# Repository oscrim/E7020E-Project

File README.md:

# E7020E-Project

# E-Toaster
Design and build a PCB to upgrade a toaster to an e-Toaster !

# Prerequisites 

* Archlinux
* Visual studio

# Implementation

For the software part we will use RUST to program the MCU.
Build with :
* Cargo
* OpenOCD

# Components

## General
* 1: Nucleo board to program our own board
* 1: USB Mini-B connector
* 1: bluetooth sensor RN 42 Series Class 2
* 1: STM32F411RET6 MCU
* 1: LM1117IMP-ADJ voltage converter
* 3: 6pins header
* 1: temp sensor LMT84
* 1: LCD screen EA DOGS102W-6
* 2: red LEDs
* 1: green LED
* 2: pushbuttons
* 2: transistors
* 1: relay 5V-230V

## Capacitors
* 2: 4.7u
* 12:  100n
* 5:   1u
* 2:   18p
* 1:   0.01u
* 2:   10u polarized

## Resistors
* 2:            4.7k
* 3:   10k
* 5:   100
* 1:   5k
* 2:   470
* 4:   3.3k
* 2:   1k
* 1:   820
* 1:   160

# Authors 

* **SCHRUB Valentin** - Hardware design and realization.

* **ROMARY Lucas** - Hardware design and realization.

* **FRISENSTAM Carl** - Software implementation.

* **RIMSBY Oscar** - Software implementation.

# Grades 

**Grade 3**:
Implement LED, push button, temperature sensor and LCD screen.

**Grade 4**:
Implement Bluetooth functionality. Write software to enable remote start of toaster. Enable LCD screen to display relevant information.

**Grade 5**:
Extend functionality of LCD screen. Additional information to be displayed. Improve remote functionality? Mobile application.

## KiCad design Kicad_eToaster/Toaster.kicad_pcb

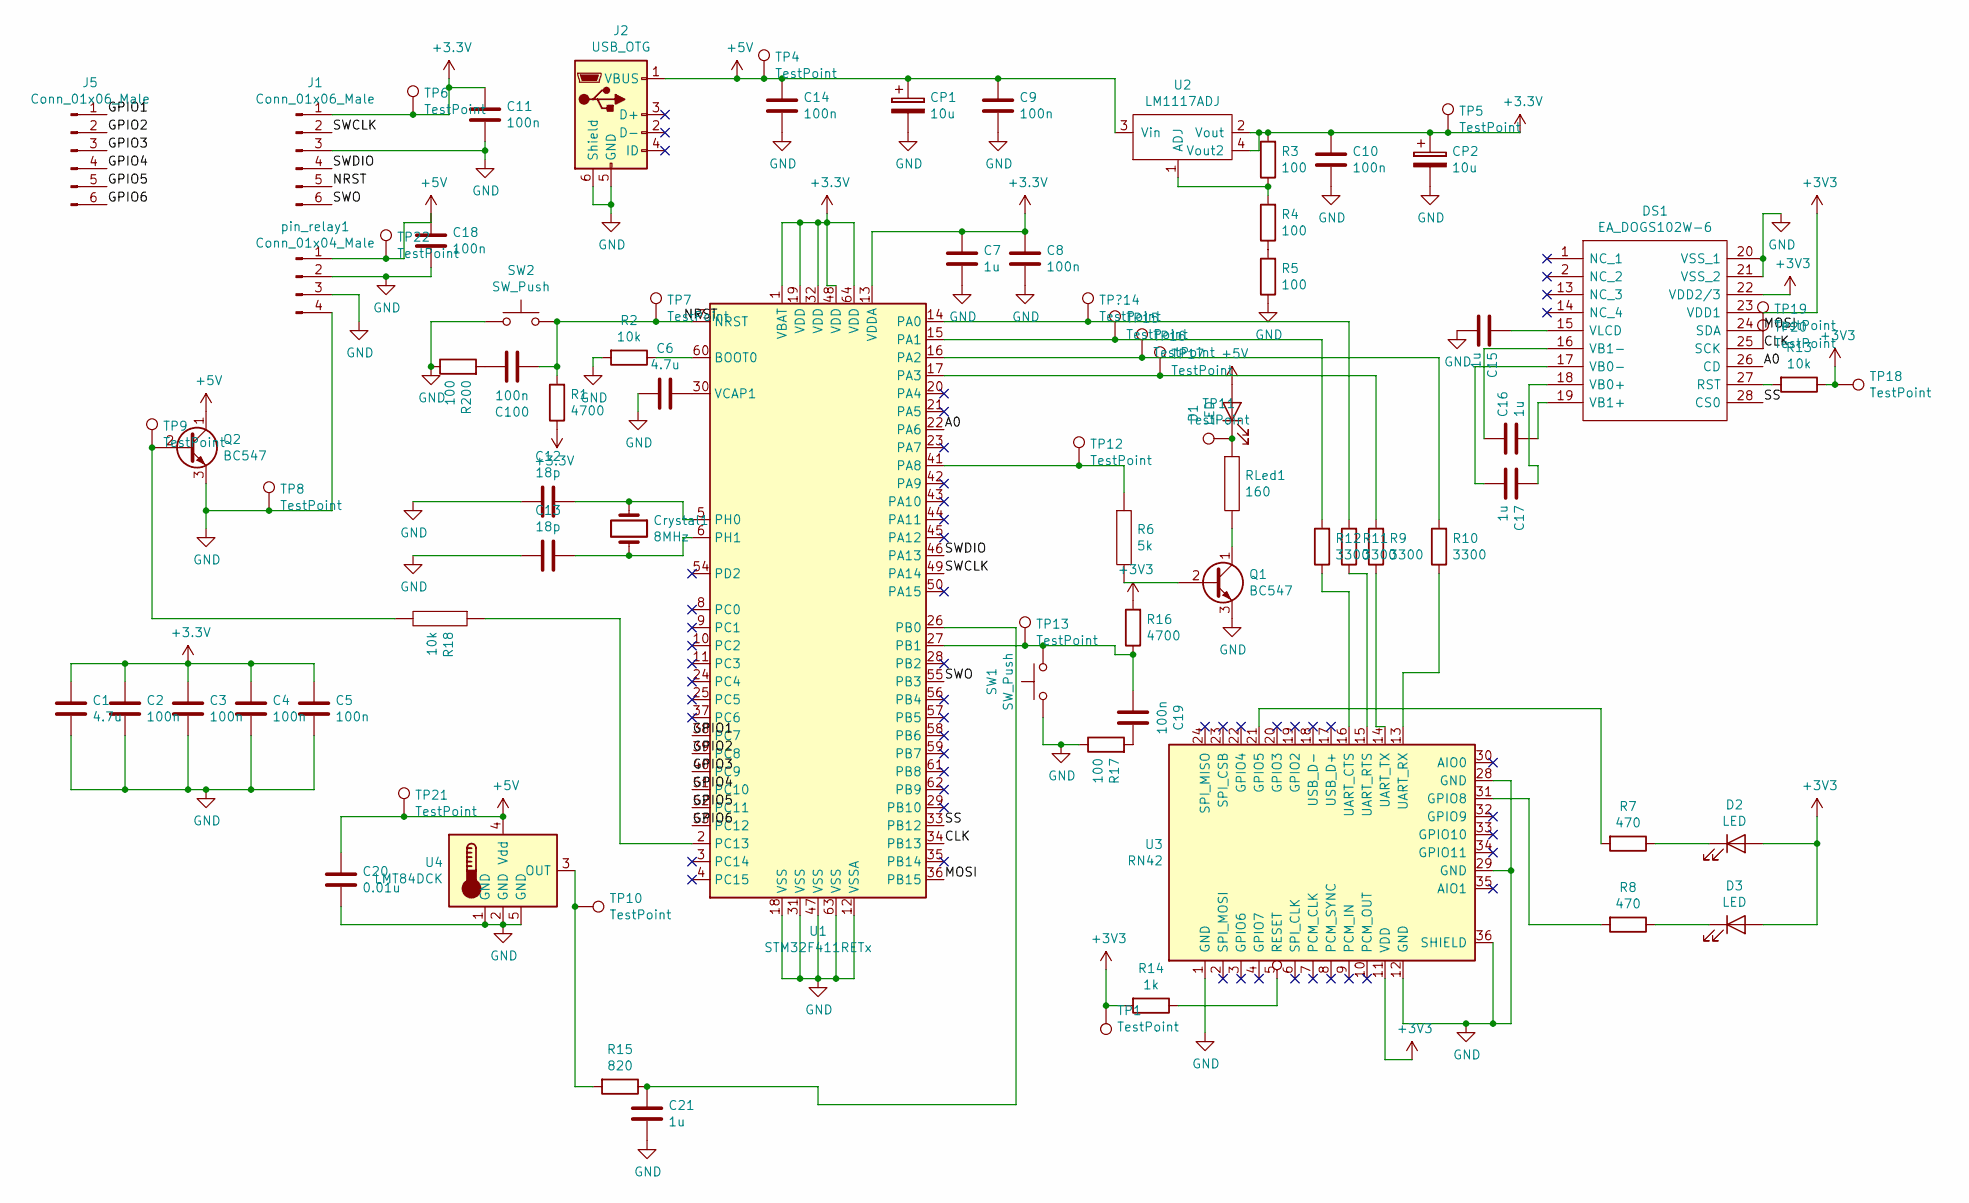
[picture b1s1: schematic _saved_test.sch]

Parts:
C1, C6: 4.7u; C_0805_2012Metric_Pad1.15x1.40mm_HandSolder
C2, C3, C4, C5, C8, C9, C10, C11, C14, C18, C19, C100: 100n; C_0805_2012Metric_Pad1.15x1.40mm_HandSolder
C7, C15, C16, C17, C21: 1u; C_0805_2012Metric_Pad1.15x1.40mm_HandSolder
C12, C13: 18p; C_0805_2012Metric_Pad1.15x1.40mm_HandSolder
C20: 0.01u; C_0805_2012Metric_Pad1.15x1.40mm_HandSolder
CP1, CP2: 10u; CP_Radial_D5.0mm_P2.00mm
Crystal1: 8MHz; Crystal_SMD_HC49-SD_HandSoldering
D1, D2, D3: LED; LED_D5.0mm
DS1: EA_DOGS102W-6; EA-DOGS102W-6; Manufacturer_Part_Number EA DOGS102W-6; Mouser Part Number 790-EADOGS102W-6
J1, J5: Conn_01x06_Male; PinHeader_1x06_P2.54mm_Vertical
J2: USB_OTG; USB_Mini-B_AdamTech_MUSB-B5-S-VT-TSMT-1_SMD_Vertical
Q1, Q2: BC547; TO-92_Inline
R1, R16: 4700; R_0805_2012Metric_Pad1.15x1.40mm_HandSolder
R2, R13, R18: 10k; R_0805_2012Metric_Pad1.15x1.40mm_HandSolder
R3, R4, R5, R17, R200: 100; R_0805_2012Metric_Pad1.15x1.40mm_HandSolder
R6: 5k; R_0805_2012Metric_Pad1.15x1.40mm_HandSolder
R7, R8: 470; R_0805_2012Metric_Pad1.15x1.40mm_HandSolder
R9, R10, R11, R12: 3300; R_0805_2012Metric_Pad1.15x1.40mm_HandSolder
R14: 1k; R_0805_2012Metric_Pad1.15x1.40mm_HandSolder
R15: 820; R_0805_2012Metric_Pad1.15x1.40mm_HandSolder
RLed1: 160; R_0805_2012Metric_Pad1.15x1.40mm_HandSolder
SW1, SW2: SW_Push; SW_PUSH_6mm_H4.3mm
TP1, TP4, TP5, TP6, TP7, TP8, TP9, TP10, TP11, TP12, TP13, TP15, TP16, TP17, TP18, TP19, TP20, TP21, TP22: TestPoint; TestPoint_Pad_1.0x1.0mm
TP?14: TestPoint; TestPoint_Pad_1.0x1.0mm
U1: STM32F411RETx; LQFP-64_10x10mm_P0.5mm
U2: LM1117ADJ; SOT-223
U3: RN42
U4: LMT84DCK; SOT-353_SC-70-5_Handsoldering
pin_relay1: Conn_01x04_Male; FanPinHeader_1x04_P2.54mm_Vertical

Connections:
+5V: C9.2, C14.2, C18.2, C20.1, CP1.1, D1.2 (A), J2.1 (VBUS), Q2.1 (C), TP4.1, TP21.1, TP22.1, U2.3 (Vin), U4.4 (Vdd), pin_relay1.1
/A0: DS1.26 (CD), U1.22 (PA6)
/CLK: DS1.25 (SCK), TP20.1, U1.34 (PB13)
/GPIO1: J5.1, U1.38 (PC7)
/GPIO2: J5.2, U1.39 (PC8)
/GPIO3: J5.3, U1.40 (PC9)
/GPIO4: J5.4, U1.51 (PC10)
/GPIO5: J5.5, U1.52 (PC11)
/GPIO6: J5.6, U1.53 (PC12)
/MOSI: DS1.24 (SDA), TP19.1, U1.36 (PB15)
/NRST: C100.2, J1.5, R1.2, SW2.2, TP7.1, U1.7 (NRST)
/SS: DS1.28 (CS0), U1.33 (PB12)
/SWCLK: J1.2, U1.49 (PA14)
/SWDIO: J1.4, U1.46 (PA13)
/SWO: J1.6, U1.55 (PB3)
GND: C1.1, C2.1, C3.1, C4.1, C5.1, C6.1, C7.1, C8.1, C9.1, C10.1, C11.1, C12.2, C13.2, C14.1, C15.1, C18.1, C20.2, C21.2, CP1.2, CP2.2, DS1.20 (VSS_1), DS1.21 (VSS_2), J1.3, J2.5 (GND), J2.6 (Shield), Q1.3 (E), Q2.3 (E), R2.2, R5.1, R17.1, R200.1, SW1.1, SW2.1, TP8.1, U1.12 (VSSA), U1.18 (VSS), U1.31 (VSS), U1.47 (VSS), U1.63 (VSS), U3.1 (GND), U3.12 (GND), U3.28 (GND), U3.29 (GND), U3.36 (SHIELD), U4.1 (GND), U4.2 (GND), U4.5 (GND), pin_relay1.2, pin_relay1.3, pin_relay1.4
unnamed: C6.2, U1.30 (VCAP1)
unnamed: C12.1, Crystal1.1, U1.5 (PH0)
unnamed: C13.1, Crystal1.2, U1.6 (PH1)
unnamed: C15.2, DS1.15 (VLCD)
unnamed: C16.1, DS1.19 (VB1+)
unnamed: C16.2, DS1.16 (VB1-)
unnamed: C17.1, DS1.17 (VB0-)
unnamed: C17.2, DS1.18 (VB0+)
unnamed: C19.1, R17.2
unnamed: C19.2, R16.1, SW1.2, TP13.1, U1.27 (PB1)
unnamed: C21.1, R15.1, U1.26 (PB0)
unnamed: C100.1, R200.2
unnamed: D1.1 (K), RLed1.1, TP11.1
unnamed: D2.1 (K), R7.1
unnamed: D3.1 (K), R8.1
unnamed: DS1.27 (RST), R13.2
unnamed: Q1.1 (C), RLed1.2
unnamed: Q1.2 (B), R6.2
unnamed: Q2.2 (B), R18.2, TP9.1
unnamed: R2.1, U1.60 (BOOT0)
unnamed: R3.1, R4.2, U2.1 (ADJ)
unnamed: R4.1, R5.2
unnamed: R6.1, TP12.1, U1.41 (PA8)
unnamed: R7.2, U3.21 (GPIO5)
unnamed: R8.2, U3.31 (GPIO8)
unnamed: R9.1, U3.14 (UART_TX)
unnamed: R9.2, TP17.1, U1.17 (PA3)
unnamed: R10.1, U3.13 (UART_RX)
unnamed: R10.2, TP16.1, U1.16 (PA2)
unnamed: R11.1, U3.15 (UART_RTS)
unnamed: R11.2, TP?14.1, U1.14 (PA0)
unnamed: R12.1, U3.16 (UART_CTS)
unnamed: R12.2, TP15.1, U1.15 (PA1)
unnamed: R14.1, U3.5 (RESET)
unnamed: R15.2, TP10.1, U4.3 (OUT)
unnamed: R18.1, U1.2 (PC13)

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
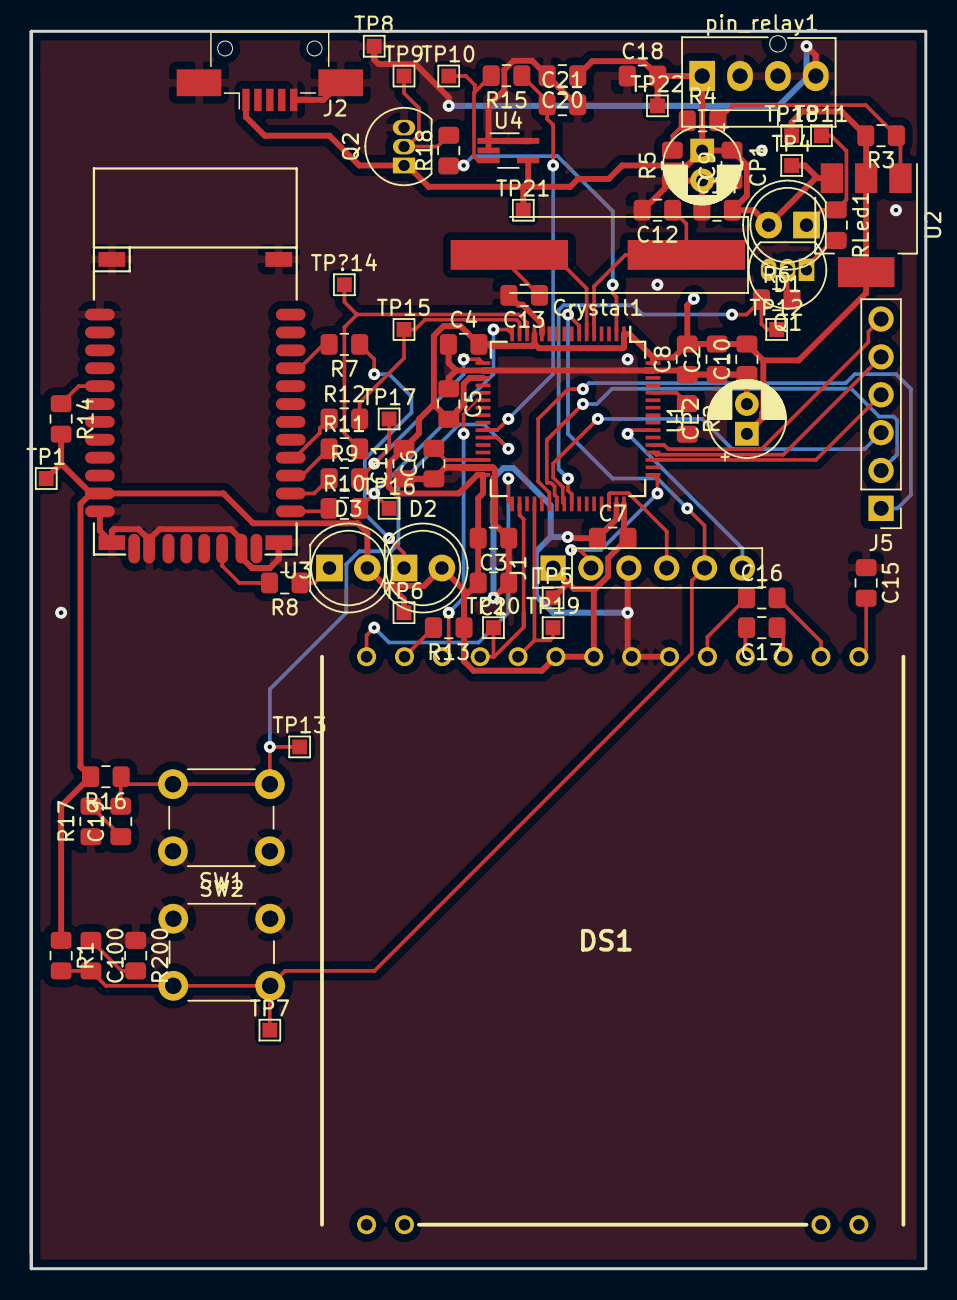
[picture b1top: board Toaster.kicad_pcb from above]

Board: 2 copper layers, 60.0 x 83.0 mm, 81 parts (0 on the bottom side), 53 nets.

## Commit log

2019-03-25 Create electronics
2019-03-25 removed dirs for Lucas
2019-03-25 added some bares
2019-03-25 added bare again
2019-03-25 added the temp-sensor code example
2019-03-26 removed all docs
2019-03-26 removed more docs
2019-03-26 added gitignore for the doc folders
2019-03-26 added temperature sensor conversion
2019-03-26 added temperature estimate
2019-03-26 Edited BT section, added temp sens and adc section
2019-03-27 bare9_1
2019-03-27 bare9_2
2019-03-27 bare10_1
2019-03-27 bare10_2
2019-03-28 last commit
2019-03-28 some work on bare10_3
2019-03-28 fix gitignore
2019-04-02 bare10_3
2019-04-02 started refzctoring spiTest into pcbProject
2019-04-09 Bluetooth test
2019-04-15 Update pcbProject.rs
    Now fills half the screen during the screen paint animation
2019-05-12 Fixed usart2, cand send and receive via bluetooth
2019-05-17 Changed the delay between half-screens
